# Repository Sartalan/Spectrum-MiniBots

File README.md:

# Proyecto MiniBots.

---

## ¿En qué consiste?

- Consiste en un proyecto en grupo creado por el grupo “Spectrum” con el objetivo de crear una serie de robots qué se movilizarán dentro de una casa y, en base a dicho recorrido “interactuaran” de forma no directa con su entorno a través de un servidor IOT entre dichos robots y la misma casa, la cuál también será inteligente y cambiará correspondientemente a la actividad de dichos robots. Los mismos datos y cambios qué sucederán en la casa también serán mostrados en pantalla a través de una web.

       ————————————————————————

## ¿Qué actividades harán?

- Cada uno de los robots tendrá una respectiva personalidad qué definirá el cómo actuará y, de forma irremediable, repercutirá el funcionamiento de dicha casa lo que conllevará a qué sucedan cosas como:

- Actividades:
    1. Prender el lavarropa
    2. Ir a sus habitaciones y cargar su batería
    3. Ir a rezar a un altar
    4. Ver la tele 
    5. Descansar
    6. Cocinar

      ————————————————————————

## ¿Cómo funcionarán los robots?

- Los robots se movilizarán por la casa a través de un sensor infrarrojo como un seguidor de línea y, cada día tendrán una actividad diferente dependiendo de sus responsabilidades del día

      ————————————————————————     

## ¿Cómo funcionará la casa?

- La casa funcionará como una casa inteligente a través de su circuito qué se compondrá principalmente de un ESP32 que sé encontrará en el altar y funcionará como mediador de datos para el servidor. A su vez, la casa tendrá ciclos de día y noches qué solamente compondrán a una semana de actividad

<aside>
🐧          Comienzo del Proyecto.

</aside>

---

### ~Tareas a realizar~

- [ ]  Crear una página web con un servidor MySql funcional
- [ ]  Crear el diseño y los planos de la maqueta donde se movilizarán los miniBots por medio de AutoCAD
- [ ]  Crear el diseño y planos en 3D de los miniBots por medio de Fusión 360
- [ ]  Crear el código de la casa
- [ ]  Crear el código de los miniBots
- [ ]  Diseñar tanto el circuito de la casa como el circuito de los miniBot

---

## <  PASOS A EJECUTAR: />

### Primera fase:

La primera fase se conformará de la creación de las ruedas base del miniBot

- **Paso 1:** Comenzar diseñando un “boceto” en 3D de un miniBot con tal de determinar su tamaño aproximado, para así establecer límites/aproximados de tamaños para tanto la maqueta, como para la plaqueta PCB

---

- Paso 2: Una vez realizado el paso anterior, comenzar simultáneamente con el PCB y la Maqueta.
- :: Paso 2.5: La maqueta deberá iniciarse vacia. Los detalles se decidirán a más tardar, lo importantes en este punto es definir su tamaño y su forma. Sus materiales se decidirán en este punto

---

- Paso 3: En este punto muy posiblemente tengamos una buena noción de hacia donde apunta el proyecto. Decidir los detalles secundarios sobre la marcha
- ::Pasó 3.5: Realizar los muy probablemente 2 PCB; El primero correspondiente a la movilidad del robot para así probar su buena funcionalidad con las ruedas tipo oruga y el otro para los sensores y el envío de datos

---

- Paso 4: Con el PCB de la movilidad ya creado, proceder a hacer diferentes pruebas de movilidad
- ::Paso 4.5: Con las ruedas creadas y el PCB hecho y la muy posiblemente buena noción de tamaño y diseño del resto de robot, enfocarse más directamente a la maqueta tanto en su diseño como en su funcionalidad

---

- Paso 5: Trabajar en simultáneo con la maqueta y el robot. El resto del proceso será parte de la segunda fase, la cuál, todavía no está documentada debido a qué se decidirá en dicho momento.

       Pero básicamente, el resto de la ejecución
       de los MiniBots consiste en trabajar en 
       simultáneo tanto con la maqueta como con 
       los MiniBots para así luego unirlos vía web.

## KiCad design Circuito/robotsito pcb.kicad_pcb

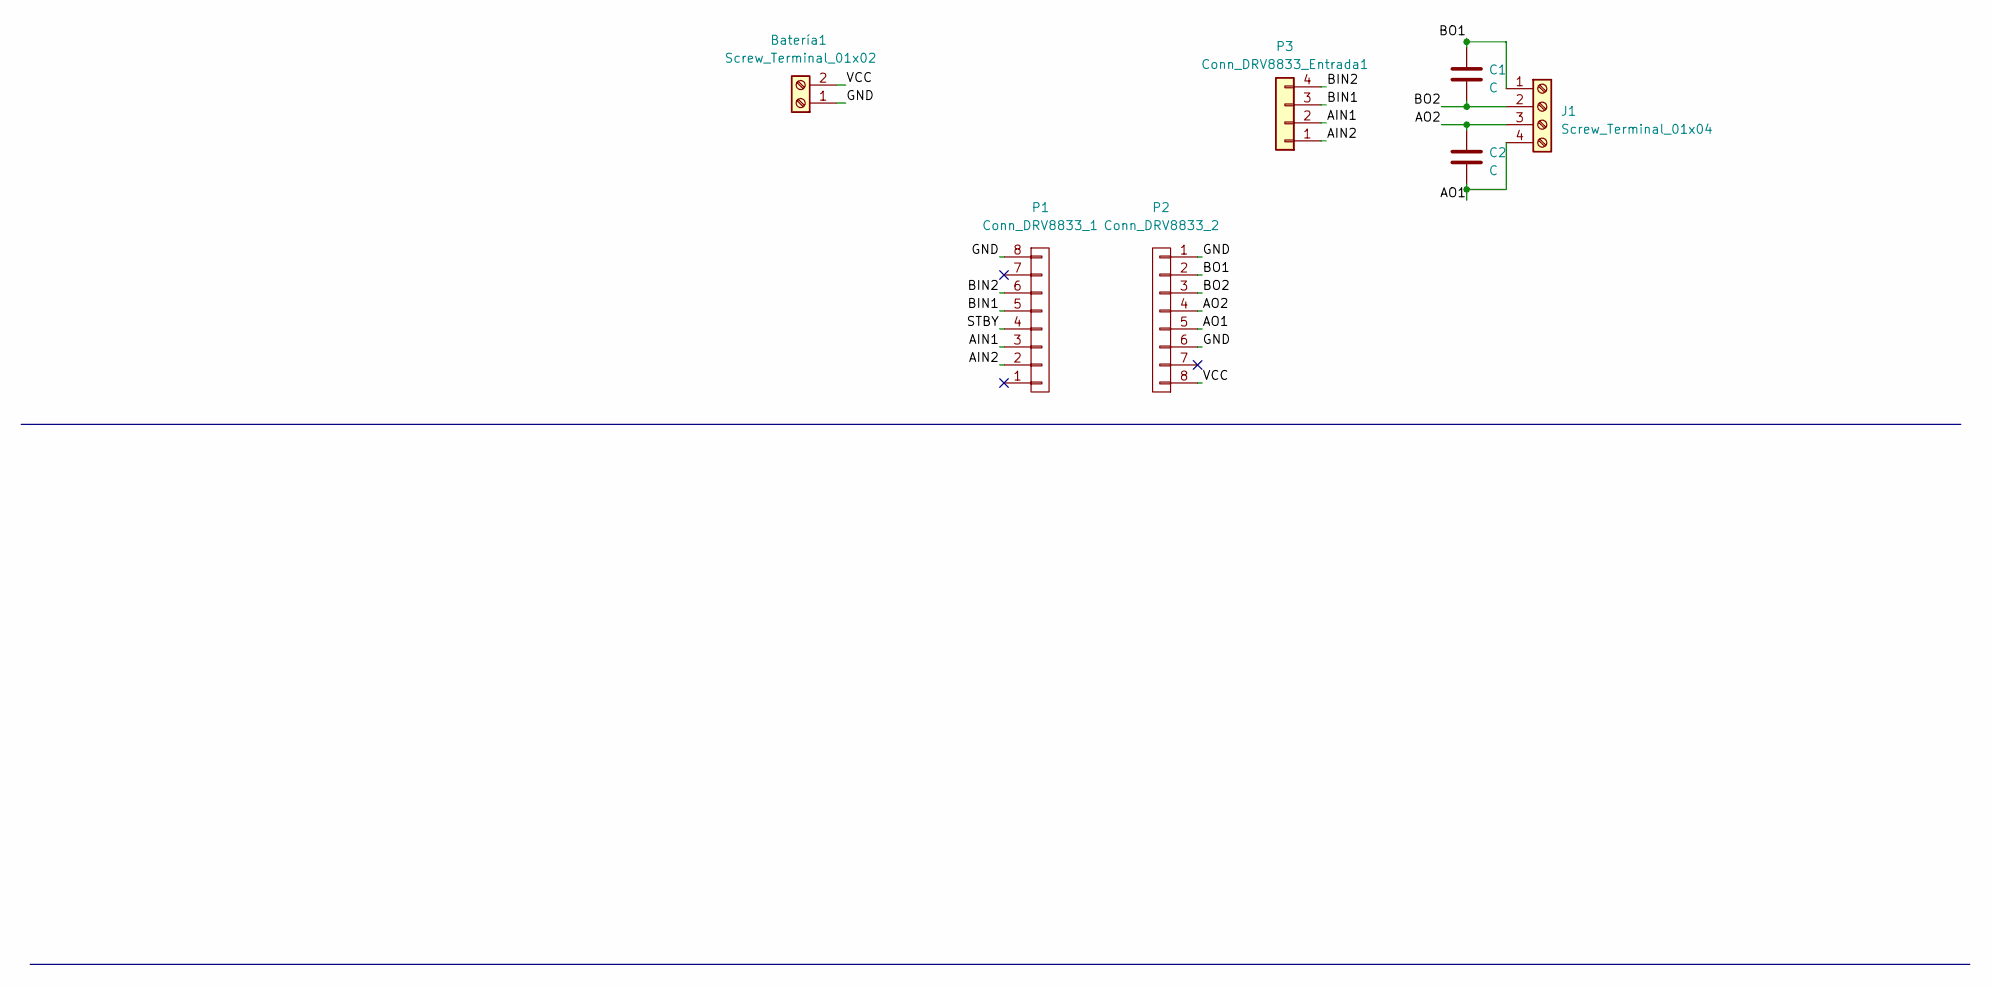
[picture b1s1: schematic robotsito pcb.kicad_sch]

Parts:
Batería1: Screw_Terminal_01x02; TerminalBlock_Altech_AK300-2_P5.00mm
C1, C2: C; C_Disc_D6.0mm_W2.5mm_P5.00mm
Conn_DRV8833_Entrada1: P3; PinHeader_1x04_P2.54mm_Vertical
J1: Screw_Terminal_01x04; PinHeader_1x04_P2.54mm_Vertical
P1: Conn_DRV8833_1; PinHeader_1x08_P2.54mm_Vertical
P2: Conn_DRV8833_2; PinHeader_1x08_P2.54mm_Vertical

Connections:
/AIN1: Conn_DRV8833_Entrada1.2, P1.3
/AIN2: Conn_DRV8833_Entrada1.1, P1.2
/AO1: C2.2, J1.4, P2.5
/AO2: C2.1, J1.3, P2.4
/BIN1: Conn_DRV8833_Entrada1.3, P1.5
/BIN2: Conn_DRV8833_Entrada1.4, P1.6
/BO1: C1.1, J1.1, P2.2
/BO2: C1.2, J1.2, P2.3
/GND: Batería1.1, P1.8, P2.1, P2.6
/STBY: P1.4
/VCC: Batería1.2, P2.8

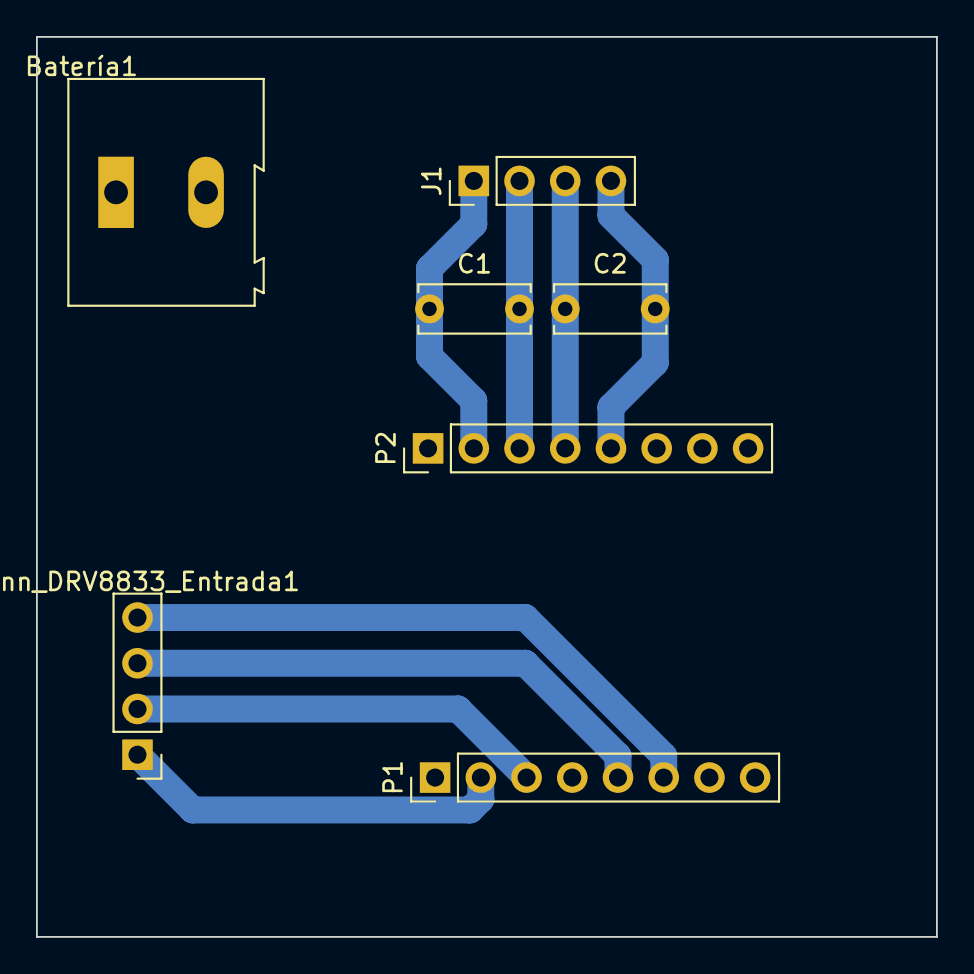
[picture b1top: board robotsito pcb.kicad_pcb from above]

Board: 2 copper layers, 50.0 x 50.0 mm, 7 parts (0 on the bottom side), 10 nets.

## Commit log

2023-08-08 cilicio1
2023-08-21 Readme Actualizado / Plan de Trabajo
2023-08-21 Rename README.md to Plan de Trabajo.md
    En principio este es un archivo de texto creado con la intención de marcarle a Spectrum como equipo, el como deberá éste de trabajar para realizar exitosamente tan ambicioso proyecto.
    Este Readme claramente no será el qué perdurará hasta el final del proyecto, solo es un paso a paso de como ejecutaremos nuestro proyecto -público- para que sí a alguien le interesa nuestro proyecto,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
2023-08-21 Agragado de README y el Plan de Trabajo
2023-08-21 Description Add to Plan de Trabajo.md
2023-09-13 Comienzo del PCB
2023-09-13 PCB v1.1
2023-09-27 Primera Versión del Código
2023-09-27 Código 0.1v
2023-10-03 Código 0.2v
2023-10-03 Código 0.3v
2023-10-05 Código 0.4v Rebuild ! Example Code WebSocket
2023-10-05 Código 0.5v ! Added control Coded
2023-10-09 Código 0.6v ! Added Leds to the Comunication
2023-10-09 Código 0.7v ! Added Controller.html
2023-10-09 Código 0.7.5v ! Code Customization Feature
2023-10-11 Código 0.8v ! REDSPYINTHEBASE?
2023-10-26 Código 0.9v ! LOL
2023-10-26 Código 0.9.1v ! Bug fix
2023-11-08 Código 0.9.5v ! GG
2023-11-08 Código 1.0v Bv
2023-11-14 Código 1.0v DE VERDAD ! Código OFICIALMENTE TERMINADO
